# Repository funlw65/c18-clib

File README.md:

[Go back to the main site](https://funlw65.github.io/)
<hr />

## :boom: Welcome!

This is work in progress! Don't use it for production! Initially, the library was made to work with both Microchip C compilers, C18 and XC8 but only for one microcontroller, PIC18F46K22 working at 64MHz speed to match an ATmega644P at16MHz (still, some libs are universal). Later, development continued only for the XC8 compiler. There are still some old files, kept for some emergencies.

For a while, Microchip made the mplabc18-v3.40-linux-full-installer.run file available for download. It is a full version, without limitations. I told to a lot of friends to get it and now, even if is not available anymore, I consider it being in the Public Domain. Many thanks to the MPLAB C18 Development Team!
But anyway, the latest version of XC8 compiler is much better now.

```
 Page done.
```

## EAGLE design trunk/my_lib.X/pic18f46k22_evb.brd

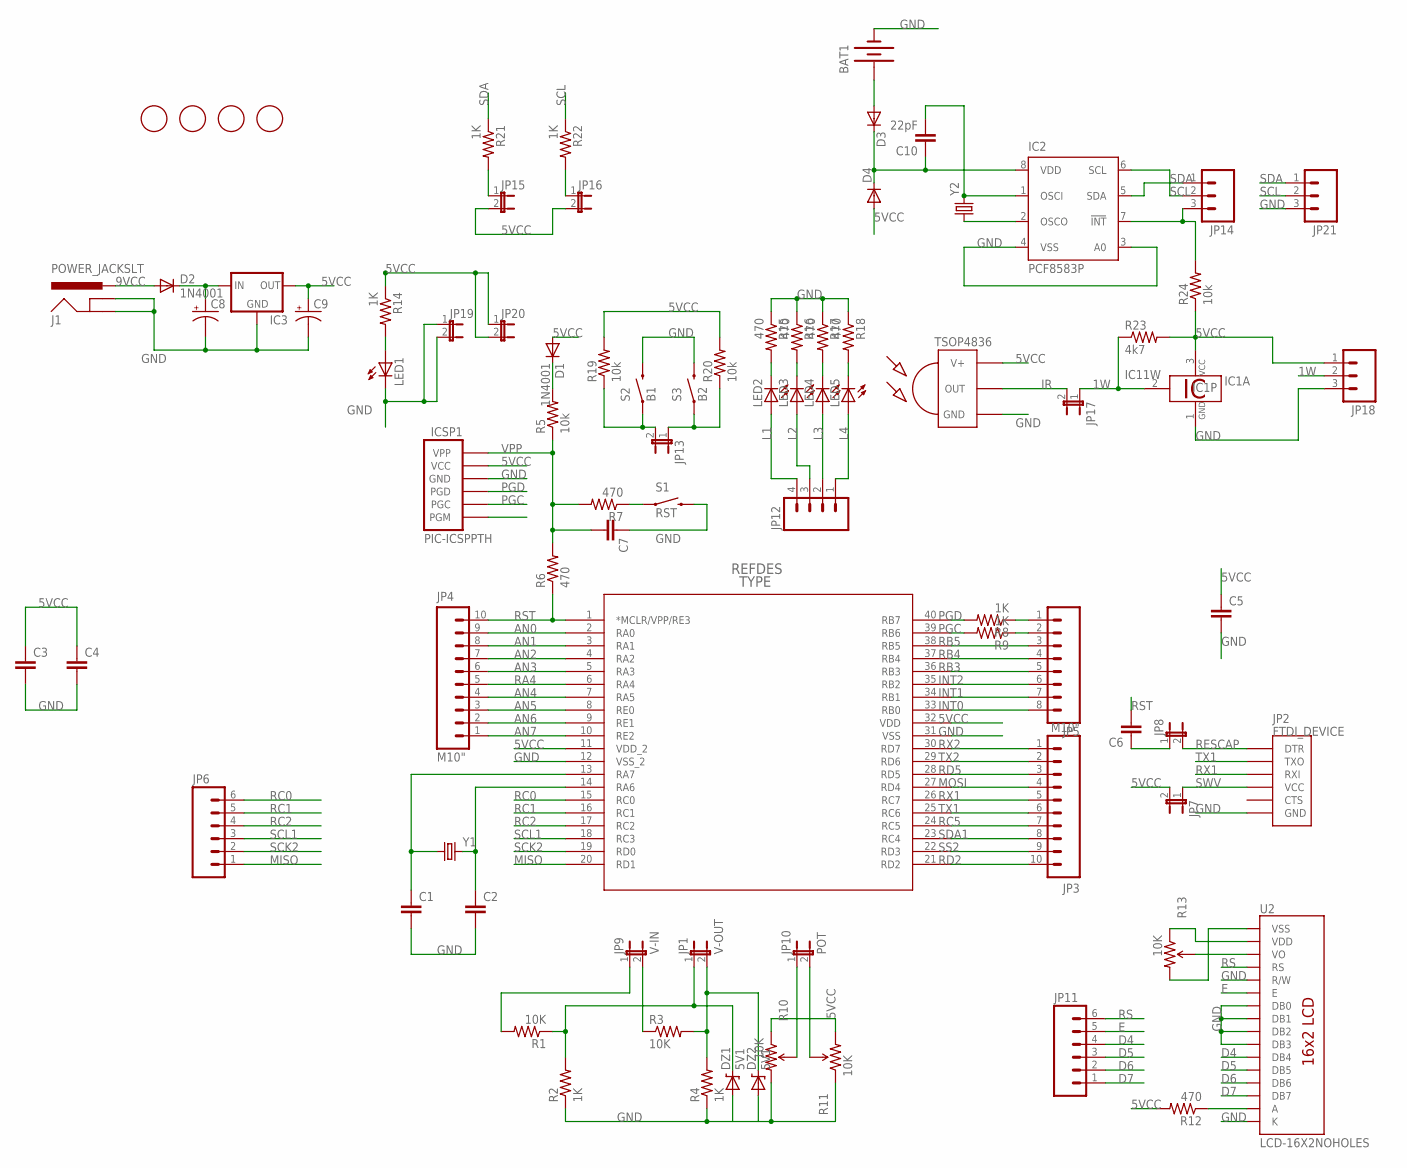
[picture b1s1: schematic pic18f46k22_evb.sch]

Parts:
BAT1: BATTERY12MM; BATTCON_12MM
C1, C2, C3, C4, C5, C6, C7: CAPPTH1; CAP-PTH-5MM
C8: CAP_POLPTH1; CPOL-RADIAL-100UF-25V
C9: CAP_POLPTH2; CPOL-RADIAL-10UF-25V
C10: 22pF; CAP-PTH-5MM
D1, D2: 1N4001; DIODE-1N4001
D3, D4: DIODE1N4148; DIODE-1N4148
DZ1, DZ2: 5V1; DIODE-ZENER
IC1: DS18B20; TO92-
IC2: PCF8583P; DIL08
IC3: V_REG_78XXSINK; TO220-IGO
ICSP1: PIC-ICSPPTH; MOLEX-1X6
J1: POWER_JACKSLT; POWER_JACK_SLOT
JP1: V-OUT; 1X02
JP2: FTDI_DEVICE; FTDI_DEVICE_SIDE
JP3, JP4: M10"; 1X10
JP5: M081X08; 1X08
JP6, JP11: M06SIP; 1X06
JP7, JP8, JP13, JP15, JP16, JP17, JP19, JP20: JUMPER-2PTH; 1X02
JP9: V-IN; 1X02
JP10: POT; 1X02
JP12: M04PTH; 1X04
JP14, JP18, JP21: M03PTH; 1X03
LED1, LED2, LED3, LED4, LED5: LED3MM
R1, R3: 10K; AXIAL-0.3
R2, R4, R8, R9, R14, R21, R22: 1K; AXIAL-0.3
R5, R19, R20, R24: 10k; AXIAL-0.3
R6, R7, R12, R15, R16, R17, R18: 470; AXIAL-0.3
R10, R11, R13: 10K; TRIM_POT_PTH
R23: 4k7; AXIAL-0.3
S1: RST; TACTILE-PTH
S2: B1; TACTILE-PTH
S3: B2; TACTILE-PTH
U1: PIC18F46K22; MICROCHIP_PDIP40_600MC
U2: LCD-16X2NOHOLES; LCD-16X2_NOHOLES
U$1, U$2, U$3, U$4: MOUNTINGHOLE3.0THIN; MOUNTINGHOLE_3.0_PLATEDTHIN
U$5: TSOP4836; TSOP18XX
Y1: CRYSTALHC49UV; HC49U-V
Y2: CRYSTALTC38H; TC38H

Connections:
1W: IC1.2 (1W), JP17.1, JP18.2, R23.P$1 (1)
5VCC: C3.1, C4.1, C5.1, C9.1 (+), D1.A, D4.A, IC1.3 (VDD), IC3.OUT, ICSP1.5 (VCC), JP7.2, JP15.2, JP16.2, JP18.1, JP20.1, JP20.2, R10.1 (CCW), R11.3 (CW), R12.P$2 (2), R13.1 (CCW), R14.P$1 (1), R19.P$2 (2), R20.P$2 (2), R23.P$2 (2), R24.P$1 (1), U1.11 (VDD_2), U1.32 (VDD), U2.2 (VDD), U$5.VCC (V+)
9VCC: D2.A, J1.PWR
AN0: JP4.9, U1.2 (RA0)
AN1: JP4.8, U1.3 (RA1)
AN2: JP4.7, U1.4 (RA2)
AN3: JP4.6, U1.5 (RA3)
AN4: JP4.4, U1.7 (RA5)
AN5: JP4.3, U1.8 (RE0)
AN6: JP4.2, U1.9 (RE1)
AN7: JP4.1, U1.10 (RE2)
D4: JP11.4, U2.11 (DB4)
D5: JP11.3, U2.12 (DB5)
D6: JP11.2, U2.13 (DB6)
D7: JP11.1, U2.14 (DB7)
E: JP11.5, U2.6 (E)
GND: BAT1.GND (-), C1.2, C2.2, C3.2, C4.2, C5.2, C7.1, C8.2 (-), C9.2 (-), DZ1.P$2 (A), DZ2.P$2 (A), IC1.1 (GND), IC2.3 (A0), IC2.4 (VSS), IC3.GND, ICSP1.4 (GND), J1.GND@1 (GNDBREAK), J1.GND@2 (GND), JP2.P$6 (GND), JP18.3, JP19.1, JP19.2, JP21.3, LED1.K (C), R2.P$1 (1), R4.P$1 (1), R10.3 (CW), R11.1 (CCW), R13.3 (CW), R15.P$1 (1), R16.P$1 (1), R17.P$1 (1), R18.P$1 (1), S1.3 (2), S2.3 (2), S3.3 (2), U1.12 (VSS_2), U1.31 (VSS), U2.1 (VSS), U2.5 (R/W), U2.7 (DB0), U2.8 (DB1), U2.9 (DB2), U2.10 (DB3), U2.16 (K), U$5.GND
INT0: JP5.8, U1.33 (RB0)
INT1: JP5.7, U1.34 (RB1)
INT2: JP5.6, U1.35 (RB2)
IR: JP17.2, U$5.OUT
L1: JP12.4, LED2.A
L2: JP12.3, LED3.A
L3: JP12.2, LED4.A
L4: JP12.1, LED5.A
MISO: JP6.1, U1.20 (RD1)
MOSI: JP3.4, U1.27 (RD4)
unnamed: C1.1, U1.13 (RA7), Y1.1
unnamed: C2.1, U1.14 (RA6), Y1.2
unnamed: D1.C, R5.P$2 (2)
unnamed: R7.P$1 (1), S1.1
unnamed: JP5.1, R8.P$1 (1)
unnamed: JP5.2, R9.P$1 (1)
unnamed: C6.1, JP8.1
unnamed: IC2.2 (OSCO), Y2.1
unnamed: DZ1.P$1 (C), JP1.1, R1.P$1 (1), R2.P$2 (2)
unnamed: DZ2.P$1 (C), JP1.2, R3.P$2 (2), R4.P$2 (2)
unnamed: JP9.2, R3.P$1 (1)
unnamed: JP9.1, R1.P$2 (2)
unnamed: C10.2, IC2.1 (OSCI), Y2.2
unnamed: JP10.1, R10.2 (WIPER)
unnamed: JP10.2, R11.2 (WIPER)
unnamed: C8.1 (+), D2.C, IC3.IN
unnamed: R13.2 (WIPER), U2.3 (VO)
unnamed: LED1.A, R14.P$2 (2)
unnamed: LED2.K (C), R15.P$2 (2)
unnamed: LED3.K (C), R16.P$2 (2)
unnamed: LED4.K (C), R17.P$2 (2)
unnamed: LED5.K (C), R18.P$2 (2)
unnamed: JP13.2, R19.P$1 (1), S2.1
unnamed: R12.P$1 (1), U2.15 (A)
unnamed: JP13.1, R20.P$1 (1), S3.1
unnamed: BAT1.PWR@1 (+), D3.A
unnamed: JP15.1, R21.P$2 (2)
unnamed: C10.1, D3.C, D4.C, IC2.8 (VDD)
unnamed: IC2.7 (!INT), JP14.3, R24.P$2 (2)
unnamed: JP16.1, R22.P$2 (2)
PGC: ICSP1.2 (PGC), R9.P$2 (2), U1.39 (RB6)
PGD: ICSP1.3 (PGD), R8.P$2 (2), U1.40 (RB7)
RA4: JP4.5, U1.6 (RA4)
RB3: JP5.5, U1.36 (RB3)
RB4: JP5.4, U1.37 (RB4)
RB5: JP5.3, U1.38 (RB5)
RC0: JP6.6, U1.15 (RC0)
RC1: JP6.5, U1.16 (RC1)
RC2: JP6.4, U1.17 (RC2)
RC5: JP3.7, U1.24 (RC5)
RD2: JP3.10, U1.21 (RD2)
RD5: JP3.3, U1.28 (RD5)
RESCAP: JP2.P$1 (DTR), JP8.2
RS: JP11.6, U2.4 (RS)
RST: C6.2, JP4.10, R6.P$1 (1), U1.1 (*MCLR/VPP/RE3)
RX1: JP2.P$3 (RXI), JP3.5, U1.26 (RC7)
RX2: JP3.1, U1.30 (RD7)
SCK2: JP6.2, U1.19 (RD0)
SCL: IC2.6 (SCL), JP14.2, JP21.2, R22.P$1 (1)
SCL1: JP6.3, U1.18 (RC3)
SDA: IC2.5 (SDA), JP14.1, JP21.1, R21.P$1 (1)
SDA1: JP3.8, U1.23 (RC4)
SS2: JP3.9, U1.22 (RD3)
SWV: JP2.P$4 (VCC), JP7.1
TX1: JP2.P$2 (TXO), JP3.6, U1.25 (RC6)
TX2: JP3.2, U1.29 (RD6)
VPP: C7.2, ICSP1.6 (VPP), R5.P$1 (1), R6.P$2 (2), R7.P$2 (2)

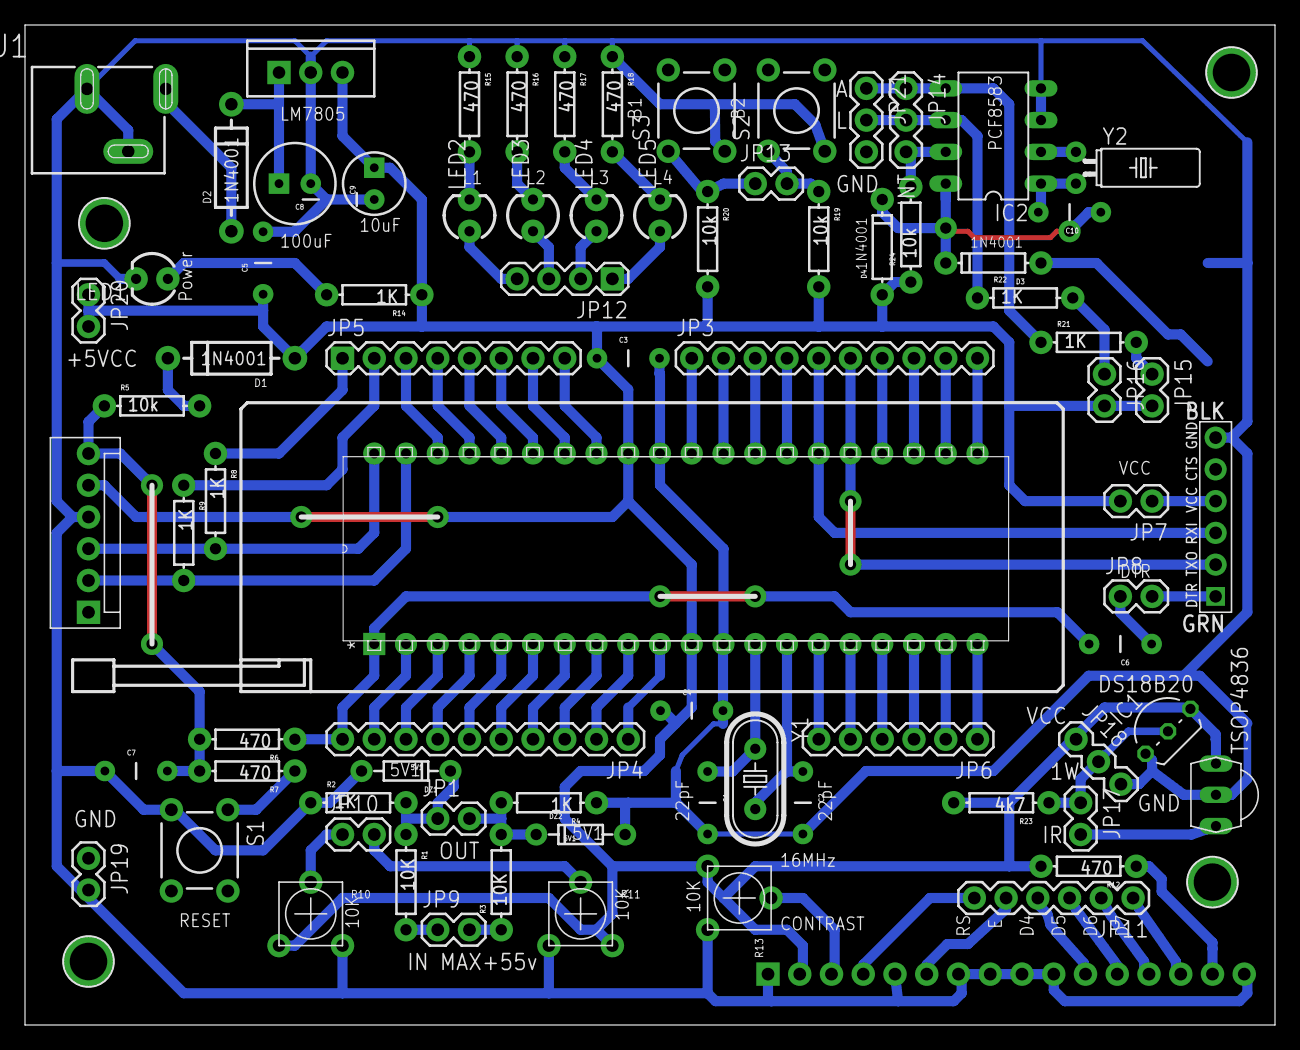
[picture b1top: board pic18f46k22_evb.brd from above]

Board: 2 copper layers, 100.0 x 80.0 mm, 84 parts (1 on the bottom side), 84 nets.

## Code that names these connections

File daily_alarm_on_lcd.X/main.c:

/* 
 * File:   main.c
 * Author: Worker
 *
 * Created on December 21, 2014, 1:39 AM
 */

/*
 * This program demonstrate the Daily alarm feature of PCF8583
 * The INT pin of PCF8583 is connected to RC0 pin of 18F46K22 along
 * with a 10K pull-up resistor. The OnBoardLED (RC2) will simulate
 * the alarm and the OnBoardButton (RA4) will stop the alarm.
 * The clock and date is displayed on a 2x16 4bit LCD display (data
 * on the upper part of port B [B4-B7], RS on RE1 and E to RE2 pins).
 * PCF8583 is connected to I2C at 0xA2 address (to make room for an
 * eventual I2C EEPROM).
 */

#include <GenericTypeDefs.h>
//#define NOBOOT 1 // uncomment if you don't use a bootloader
// enable one of the following seven boards
#define ROSSO_SER 1 //(18F46K22, 16MHz crystal, 64MHz, BootBTN = RA4, BootLED = RC2)
//#define PINGUINOP8B2_HID 2 //(18F4550, 20MHz crystal, 48MHz, BootBTN and BootLED uses RC2)
//#define PINGUINOP8B2_CDC 3 //(18F4550, 20MHz crystal, 48MHz, BootBTN and BootLED uses RC2)
//#define PINGUINOP8B3_HID 4 //(18F4550, 20MHz crystal, 48MHz, BootBTN = RA4, BootLED = RC2)
//#define PINGUINOP8B3_CDC 5 //(18F4550, 20MHz crystal, 48MHz, BootBTN = RA4, BootLED = RC2)
//#define FREEJALDUINO_CDC 6 //(18F2550, 20MHz crystal, 48MHz, UserLED1 = RA4, UserLED2 = RC2)
//#define FREEJALDUINO_HID 7 //(18F2550, 20MHz crystal, 48MHz, UserLED1 = RA4, UserLED2 = RC2)
// disable following line if your hardware differs
#define ONBOARD 1 // enable the default onboard definitions
#include <rosso.h> // processor type, speed, configuration bits, hardware, app_offset.
#include <rosso_conversion.h>
#define I2C_SCL_DIR TRISCbits.RC3 // note that this is for 18F46k22
#define I2C_SDA_DIR TRISCbits.RC4
//#define I2C_SCL_DIR TRISBbits.RB1 // note that this is for 18F4550
//#define I2C_SDA_DIR TRISBbits.RB0
#include <rosso_i2c_master.h>
#define PCF8583_USE_I2C
#define PCF8583_PHYSICAL_ADDRESS 0xA2 // 0x00 may be used by I2C EEPROM
#include <rosso_pcf8583.h>
//this time we are using the lcd library defaults for pinout
#include <rosso_delays.h> // required by LCD lib. bellow
#include <rosso_lcd4.h>

UINT8 s[4]; // buffer used for conversions

// declaring the headers for the interrupt functions
void
#ifdef __XC8
interrupt
#endif
high_isr(void);

void
#ifdef __XC8
interrupt low_priority
#endif
low_isr(void);

#ifdef __18CXX
#ifndef NOBOOT
#pragma romdata bootloader = 0x6
const rom char bootloader[APP_START - 0x6];
extern void _startup(void);

#pragma code AppVector = APP_START

void AppVector(void) {
    _asm GOTO _startup _endasm
}

#pragma code AppHighIntVector = APP_HINT

void AppHighIntVector(void) {
    _asm
    GOTO high_isr // branch to the high_isr()
            _endasm
}

#pragma code AppLowIntVector = APP_LINT

void low_vector(void) {
    _asm
    GOTO low_isr // branch to the low_isr()
            _endasm
}
#endif

#pragma code  // return to the default // code section
#endif

void main() {
    UINT8 current_sec = 0, old_sec = 0;
    AllDigital(); // all pins digital
#ifdef ONBOARD
    OnBoardLED_dir = 0; //output
    OnBoardButton_dir = 1; //input
    OnBoardLED = 0;
#endif
    //ei(); // enable general interrupts if needed
    // Add other initializations you may have...
    i2c_init(I2C_100KHZ);
    lcd_init(LCD_HD44780);
    // set the pin who sense the interrupt from RTC Alarm
    TRISCbits.RC0 = 1; // set as input
    // =====================================================================
    // if you need to set the RTC, uncomment the following and run once
    RTC_seconds = 40; // 0 to 59
    RTC_minutes = 59; // 0 to 59
    RTC_hours = 23; // 0 to 23
    RTC_day = 13; // 1 to 31
    RTC_month = 5; // 1 to 12
    RTC_century = 20; //
    RTC_year = 14; // 0 to 99
    RTC_dayofweek = 2; // 0 to 6 (Sun, Mon, etc..)
    RTC_leapyear = 2; // 0 to 3 (0 - is leapyear and 1,2,3 not)
    // 2012 was leapyear    ( leapyear = 0)
    // 2014 is not leapyear ( leapyear = 2)
    //
    pcf8583_set_datetime(RTC_hours, RTC_minutes, RTC_seconds, RTC_dayofweek, RTC_day, RTC_month, RTC_leapyear, RTC_century, RTC_year);
    // =====================================================================

    // =================== SET THE ALARM ===================================
    pcf8583_en_dis_alarm(PCF8583_DAILY_ALARM);
    pcf8583_set_alarm_time(0,0,0); // alarm at midnight :-P
    // =====================================================================

    while (1) {
        // Add your repeating code...
        pcf8583_get_datetime(&RTC_hours, &RTC_minutes, &RTC_seconds, &RTC_dayofweek, &RTC_day, &RTC_month, &RTC_leapyear, &RTC_century, &RTC_year);
        current_sec = RTC_seconds;
        if(current_sec != old_sec){
            old_sec = current_sec;
            // show time
            lcd_cursor_position(0, 0);
            byte2dec(RTC_hours, s);
            if(s[1] == ' ') _lcd_write_data('0');
            else _lcd_write_data(s[1]);
            _lcd_write_data(s[2]);
            _lcd_write_data(':');
            byte2dec(RTC_minutes, s);
            if(s[1] == ' ') _lcd_write_data('0');
            else _lcd_write_data(s[1]);
            _lcd_write_data(s[2]);
            _lcd_write_data(':');
            byte2dec(RTC_seconds, s);
            if(s[1] == ' ') _lcd_write_data('0');
            else _lcd_write_data(s[1]);
            _lcd_write_data(s[2]);
            // show date on the second line
            lcd_cursor_position(1, 0);
            byte2dec(RTC_day, s);
            if(s[1] == ' ') _lcd_write_data('0');
            else _lcd_write_data(s[1]);
            _lcd_write_data(s[2]);
            _lcd_write_data('/');
            byte2dec(RTC_month, s);
            if(s[1] == ' ') _lcd_write_data('0');
            else _lcd_write_data(s[1]);
            _lcd_write_data(s[2]);
            _lcd_write_data('/');
            byte2dec(RTC_century, s);
            _lcd_write_data(s[1]);
            _lcd_write_data(s[2]);
            byte2dec(RTC_year, s);
            _lcd_write_data(s[1]);
            _lcd_write_data(s[2]);
        }
        if(PORTCbits.RC0 == 0) OnBoardLED = 1; // signal the alarm
        else OnBoardLED = 0;
        if(OnBoardButton == 0){ // if user btn pressed, stop alarm
            OnBoardLED = 0;
            pcf8583_stop_alarm();
        }
    }
}

#ifdef __18CXX
#pragma interrupt high_isr
#endif

void
#ifdef __XC8
interrupt
#endif
high_isr(void) {
    //
}

#ifdef __18CXX
#pragma interruptlow low_isr
#endif

void
#ifdef __XC8
interrupt low_priority
#endif
low_isr(void) {
    //
}

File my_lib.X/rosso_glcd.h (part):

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
// READ Command Port Bits
#ifndef GLCD_DI_IN
#define GLCD_DI_IN         PORTEbits.RE0		// D/I Pin
#endif
#ifndef GLCD_RW_IN
#define GLCD_RW_IN         PORTEbits.RE1		// R/W Pin
#endif
#ifndef GLCD_EN_IN
#define GLCD_EN_IN         PORTEbits.RE2		// EN  Pin
#endif
#ifndef GLCD_CS1_IN
#define GLCD_CS1_IN        PORTCbits.RC0		// CS1 Pin
#endif
#ifndef GLCD_CS2_IN
#define GLCD_CS2_IN        PORTCbits.RC1		// CS2 Pin
#endif
#ifndef GLCD_RS_IN
#define GLCD_RS_IN         PORTDbits.RD2		// RS  Pin
#endif

// Command Port Bits Direction
#ifndef GLCD_DI_DIR
#define GLCD_DI_DIR         TRISEbits.RE0		
#endif
#ifndef GLCD_RW_DIR
#define GLCD_RW_DIR         TRISEbits.RE1		
#endif
#ifndef GLCD_EN_DIR
#define GLCD_EN_DIR         TRISEbits.RE2		
#endif
#ifndef GLCD_CS1_DIR
#define GLCD_CS1_DIR        TRISCbits.RC0		
#endif
#ifndef GLCD_CS2_DIR
#define GLCD_CS2_DIR        TRISCbits.RC1		
#endif
#ifndef GLCD_RS_DIR
#define GLCD_RS_DIR         TRISDbits.RD2		
#endif

#define GLCD_CHIP1            0x00
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
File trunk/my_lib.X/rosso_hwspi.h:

/* 
 * File:   rosso_spi_master.h
 * Author: MCHP
 * Adapted by: Vasile Guta Ciucur
 *
 * Created on December 28, 2014, 3:15 PM
 */

#ifndef ROSSO_HWSPI_H
#define	ROSSO_HWSPI_H

#define SPI_SDO_DIR TRISCbits.RC5
#define SPI_SDI_DIR TRISCbits.RC4
#define SPI_CLK_DIR TRISCbits.RC3
#define SPI_SS_DIR  TRISAbits.RA5

#ifndef SSPENB
typedef enum{
    SMPMID, // Input data sample at middle of data out
    SMPEND = 0b10000000 // Input data sample at end of data out
} SPIPHASE;

typedef enum{
    MODE_00,
    MODE_01,
    MODE_10,
    MODE_11
} SPIMODE;

#define   SSPENB        0b00100000           // Enable serial port and configures SCK, SDO, SDI

typedef enum{
    SPI_FOSC_4,
    SPI_FOSC_16,
    SPI_FOSC_64,
    SPI_FOSC_TMR2,
    SLV_SSON,
    SLV_SSOFF
} SPISPEED;
#endif

#define EnableIntSPI (PIE1bits.SSP1IE = 1)
#define DisableIntSPI (PIE1bits.SSP1IE = 0)
#define SetPriorityIntSPI(priority) (IPR1bits.SSP1IP = priority)
#define SPI_Clear_Intr_Status_Bit (PIR1bits.SSP1IF = 0)
#define SPI_Intr_Status (PIR1bits.SSP1IF)
#define SPI_Clear_Recv_OV (SSP1CONbits.SSPOV = 0)
#define CloseSPI() (SSP1CON1 &=0xDF)
#define DataRdySPI() (SSP1STATbits.BF)

void SPI_init(SPISPEED spi_rate, SPIMODE bus_mode, SPIPHASE smp_phase) {
    SSPSTAT &= 0x3F;                // power on state
    SSPCON1 = 0x00;                 // power on state
    SSPCON1 |= spi_rate;            // select serial mode
    SSPSTAT |= smp_phase;           // select data input sample phase

    if(bus_mode == 0) SSPSTATbits.CKE = 1; // data transmitted on falling edge
    else if(bus_mode == 2){
        SSPSTATbits.CKE = 1; // data transmitted on rising edge
        SSPCON1bits.CKP = 1; // clock idle state high
    }
    else if(bus_mode == 3) SSPCON1bits.CKP = 1; // clock idle state high
    //set SPI pins directions;
    if(spi_rate == SLV_SSON){
        SPI_CLK_DIR = 1;
        SPI_SS_DIR = 1;
    }
    else if(spi_rate == SLV_SSOFF) SPI_CLK_DIR = 1;
    else SPI_CLK_DIR = 0;
    SPI_SDO_DIR = 0;
    SPI_SDI_DIR = 1;
    SSPCON1 |= SSPENB; // enable synchronous serial port
}

#define SPI_Low_Speed()  CloseSPI();SPI_init(SPI_FOSC_64, MODE_00, SMPEND);
#define SPI_High_Speed() CloseSPI();SPI_init(SPI_FOSC_4,  MODE_00, SMPEND);

UINT8 SPI_read(void) {
    UINT8 TempVar;
    TempVar = SSPBUF; // Clear BF
    PIR1bits.SSPIF = 0; // Clear interrupt flag
    SSPBUF = 0x00; // initiate bus cycle
    //while ( !SSPSTATbits.BF );                  // wait until cycle complete
    while (!PIR1bits.SSPIF); // wait until cycle complete
    return ( SSPBUF); // return with byte read
}

INT8 SPI_write(UINT8 data_out) {
    UINT8 TempVar;
    TempVar = SSPBUF; // Clears BF
    PIR1bits.SSPIF = 0; // Clear interrupt flag
    SSPCON1bits.WCOL = 0; //Clear any previous write collision
    SSPBUF = data_out; // write byte to SSPBUF register
    if (SSPCON1 & 0x80) // test if write collision occurred
        return ( -1); // if WCOL bit is set return negative #
    else
        //while( !SSPSTATbits.BF );  // wait until bus cycle complete
        while (!PIR1bits.SSPIF); // wait until bus cycle complete
    return ( 0); // if WCOL bit is not set return non-negative#
}

#endif	/* ROSSO_HWSPI_H */

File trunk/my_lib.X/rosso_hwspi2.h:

/* 
 * File:   rosso_hwspi2.h
 * Author: MCHP
 * Adapted by: Vasile Guta Ciucur
 *
 * Created on December 29, 2014, 2:51 PM
 */

#ifndef ROSSO_HWSPI2_H
#define	ROSSO_HWSPI2_H

#define SPI_SDO2_DIR TRISDbits.RD2
#define SPI_SDI2_DIR TRISDbits.RD1
#define SPI_CLK2_DIR TRISDbits.RD0
#define SPI_SS2_DIR  TRISDbits.RD3

#ifndef SSPENB
typedef enum{
    SMPMID, // Input data sample at middle of data out
    SMPEND = 0b10000000 // Input data sample at end of data out
} SPIPHASE;

typedef enum{
    MODE_00,
    MODE_01,
    MODE_10,
    MODE_11
} SPIMODE;

#define   SSPENB        0b00100000           // Enable serial port and configures SCK, SDO, SDI

typedef enum{
    SPI_FOSC_4,
    SPI_FOSC_16,
    SPI_FOSC_64,
    SPI_FOSC_TMR2,
    SLV_SSON,
    SLV_SSOFF
} SPISPEED;
#endif

#define EnableIntSPI2 (PIE3bits.SSP2IE = 1)
#define DisableIntSPI2 (PIE3bits.SSP2IE = 0)
#define SetPriorityIntSPI2(priority) (PIE3bits.SSP2IE = 0)
#define SPI2_Clear_Intr_Status_Bit (PIR3bits.SSP2IF = 0)
#define SPI2_Intr_Status (PIR3bits.SSP2IF)
#define SPI2_Clear_Recv_OV (SSP2CONbits.SSPOV = 0)
#define CloseSPI2() (SSP2CON1 &=0xDF)
#define DataRdySPI2() (SSP2STATbits.BF)

void SPI2_init(SPISPEED spi_rate, SPIMODE bus_mode, SPIPHASE smp_phase) {
    SSP2STAT &= 0x3F;                // power on state
    SSP2CON1 = 0x00;                 // power on state
    SSP2CON1 |= spi_rate;            // select serial mode
    SSP2STAT |= smp_phase;           // select data input sample phase

    if(bus_mode == 0) SSP2STATbits.CKE = 1; // data transmitted on falling edge
    else if(bus_mode == 2){
        SSP2STATbits.CKE = 1; // data transmitted on rising edge
        SSP2CON1bits.CKP = 1; // clock idle state high
    }
    else if(bus_mode == 3) SSP2CON1bits.CKP = 1; // clock idle state high
    //set SPI pins directions;
    if(spi_rate == SLV_SSON){
        SPI_CLK2_DIR = 1;
        SPI_SS2_DIR = 1;
    }
    else if(spi_rate == SLV_SSOFF) SPI_CLK2_DIR = 1;
    else SPI_CLK2_DIR = 0;
    SPI_SDO2_DIR = 0;
    SPI_SDI2_DIR = 1;
    SSP2CON1 |= SSPENB; // enable synchronous serial port
}

#define SPI2_Low_Speed()  CloseSPI2();SPI2_init(SPI_FOSC_64, MODE_00, SMP_END);
#define SPI2_High_Speed() CloseSPI2();SPI2_init(SPI_FOSC_4,  MODE_00, SMP_END);

UINT8 SPI2_read(void) {
    UINT8 TempVar;
    TempVar = SSP2BUF;       //Clear BF
    PIR3bits.SSP2IF = 0;     //Clear interrupt flag
    SSP2BUF = 0x00;          // initiate bus cycle
    //while ( !SSP2STATbits.BF );                // wait until cycle complete
    while(!PIR3bits.SSP2IF); //wait until cycle complete
    return ( SSP2BUF );      // return with byte read
}

INT8 SPI2_write(UINT8 data_out) {
    UINT8 TempVar;
    TempVar = SSP2BUF; // Clears BF
    PIR3bits.SSP2IF = 0; // Clear interrupt flag
    SSP2CON1bits.WCOL = 0; //Clear any previous write collision
    SSP2BUF = data_out; // write byte to SSP2BUF register
    if (SSP2CON1 & 0x80) // test if write collision occurred
        return ( -1); // if WCOL bit is set return negative #
    else
        // while( !SSP2STATbits.BF ); // wait until bus cycle complete
        while (!PIR3bits.SSP2IF); //wait until bus cycle complete
    return ( 0); // if WCOL bit is not set return non-negative#
}



#endif	/* ROSSO_HWSPI2_H */

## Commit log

2014-06-26 Initial directory structure.
2014-06-26 The library container...
2014-06-28 First headers and the skeletal app.
2014-06-28 Other remaining files...
2014-06-28 18F46K22 - Blink a LED (uses a serial bootloader)
2014-06-28 First project on "Il Pinguino Rosso" board with C18...
2014-06-28 more comments in main file
2014-06-28 more source comments...
2014-06-28 removed the C++ conditionals
2014-06-28 Changed F_CPU with _XTAL_FREQ
2014-06-29 Changed the code to be portable across compilers.
2014-06-29 Repaired some leftovers from previous change...
2014-12-08 Added mydelay_us(x) and mydelay_ms(x) parametric delay functions for both PIC18F4550 at 48MHz and PIC18F46K22 at 64MHz.
2014-12-09 Corrected some non-sense code about previous functions
2014-12-09 Added non-blocking delays with tmr0
2014-12-09 Added example for non-blocking delays with tmr0
2014-12-09 - Stripped the MPLAB C18 support (code would have been unmanageable); - Improved the rosso_isr_delays library for sloted, millis or both types of non blocking delays.
2014-12-09 Demo App for sloted non-blocking delays
2014-12-09 Demo App for millis (Arduino like) non-blocking delays
2014-12-10 Added Hardware I2C Master libraries
2014-12-10 Added back the support for the MPLAB C18 compiler but on separate files. The main development offers support exclusively for MPLAB XC8.
2014-12-10 Added the development board based on PIC18F46K22
2014-12-13 - Added functions for hardware serial peripheral 1 and 2; - refactored rosso.h, rosso_delays.h and started the work at PCF8583 functions (WIP)
2014-12-13 Added back support for MPLAB C18
2014-12-13 Removed a stray function
2014-12-15 New additions and bug fixes...
2014-12-15 Deleting stray projects...
2014-12-15 Added 500 nano seconds delay, used for LCD commands...
2014-12-17 Fixed some bugs, added some functions in conversion library; Added LCD 4bit library, for displays with 8, 16 or 20 chars and 1, 2 or 4 lines.
2014-12-17 Added LCD example (Hello World! classic). Both XC8 and C18 Microchip compilators gets beaten by JALv2 compiler at smallest code size.
2014-12-17 removing orphaned projects
2014-12-17 just to save the temporary work from linux to windows... ignore it!
2014-12-18 Finally, finished adding RTC PCF8583 clock functions.
2014-12-18 Rectified a typo
2014-12-18 Corrections at schematic and pcb of the evaluation board based on PIC18F46K22
2014-12-18 Activated a code line on PCF8583 library, which signals if you make a wrong configuration.
2014-12-18 Repaired tons of errors in PCF8583 and I2C master libraries.
2014-12-18 Added pcf8583_lcd program which displays the time and date on 2x16 lcd. It demonstrates the functionality of pcf8583, lcd, i2c master, conversions and delays libraries.
2014-12-18 minor modifications in i2c and serial libraries...
2014-12-18 Added pcf8583_serial application, which sends the time and date on serial port.
2014-12-19 Added schematic for lcd_helloworld example.
2014-12-19 Repaired some miss guiding ...
2014-12-19 some clean-ups
2014-12-21 This program demonstrate the Daily alarm feature of PCF8583
2014-12-21 More details included in the comments. Use PIC18F46K22_evb evaluation board as reference (and add the extra connections required - maybe a specific schematic will be delivered somewhere in time)
2014-12-21 This program demonstrate the Weekly alarm feature of PCF8583
2014-12-21 Repaired and error that wouldn't allow Weekly alarms... Well, I was spoiled by JALv2 compiler with features that MCHP C compiler doesn't have...
2014-12-21 Forgot to uncomment the error message...
2014-12-22 Added strong typing in some parts of I2C, PCF8583 and LCD libraries.
2014-12-22 Changed parameter types of pcf8583_set_alarm_weekdays function in PCF8583 library.
2014-12-22 Small cosmetisation.
2014-12-29 Added hardware SPI
2014-12-30 Corrected some wrong compilation conditionals on hardware SPI headers.
2015-01-04 Starting with this revision, the library will provide support exclusively for PIC18F46K22 as this project is tested for the "Il Pinguino Rosso" board.
2015-01-04 Adding PWM - work in progress...
2015-01-04 Project updated accordingly...
2015-01-04 Modified rosso_lcd4.h - now the compiled code is 10 bytes smaller.
2015-02-07 PWM done
2015-02-07 added graphic lcd but without fonts yet...
2015-02-11 Added Dharmani's FAT32 library - now in the process to remove MPLAB C18 compatibility and PLIB dependence
2015-02-11 Added a test program for Dharmani's FAT32 library - not tested yet.
2015-02-13 Added a string function, not tested on real hardware.
2015-02-13 Added a test program for FAT32 - not tested yet on real hardware
2015-03-28 first svn commit on github
2015-03-28 corrected the template file
2015-03-28 adding some old files for reference
2016-05-01 Added kicad schematic
2016-05-01 Added bootloader in assembler for PIC18F46K22. It uses a switch on RA4 to enter in boot mode at startup, and a LED on RC2 to signal the fact that the bootloader is in control.
2016-05-01 Create README.md
    for the serial bootloader of PIC18F46K22.
2016-05-01 Added the cache library (remove the .txt extension when using it) of the kicad project.
2016-05-01 Added the reference design (kicad project) for the development board based on PIC18F46K22.
2016-05-01 Cosmetic changes for the main template.
2016-05-04 Added kicad schematic.
2016-05-22 Added ADC library and adapted for v1.37
2016-05-22 Added ADC on lcd example
2016-05-25 Reverted types to standard as here, support for MPLAB C18 is no more...
2016-07-15 test petitfatfs... not working for now...
2017-04-22 Set theme jekyll-theme-midnight

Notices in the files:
parts and their libraries:
SparkFun-Electromechanical: Licensing: CC v3.0 Share-Alike You are welcome to use this library for commercial purposes.
